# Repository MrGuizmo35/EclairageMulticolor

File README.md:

# EclairageMulticolor
Eclairage led RGB pour la petite maison de ma fille

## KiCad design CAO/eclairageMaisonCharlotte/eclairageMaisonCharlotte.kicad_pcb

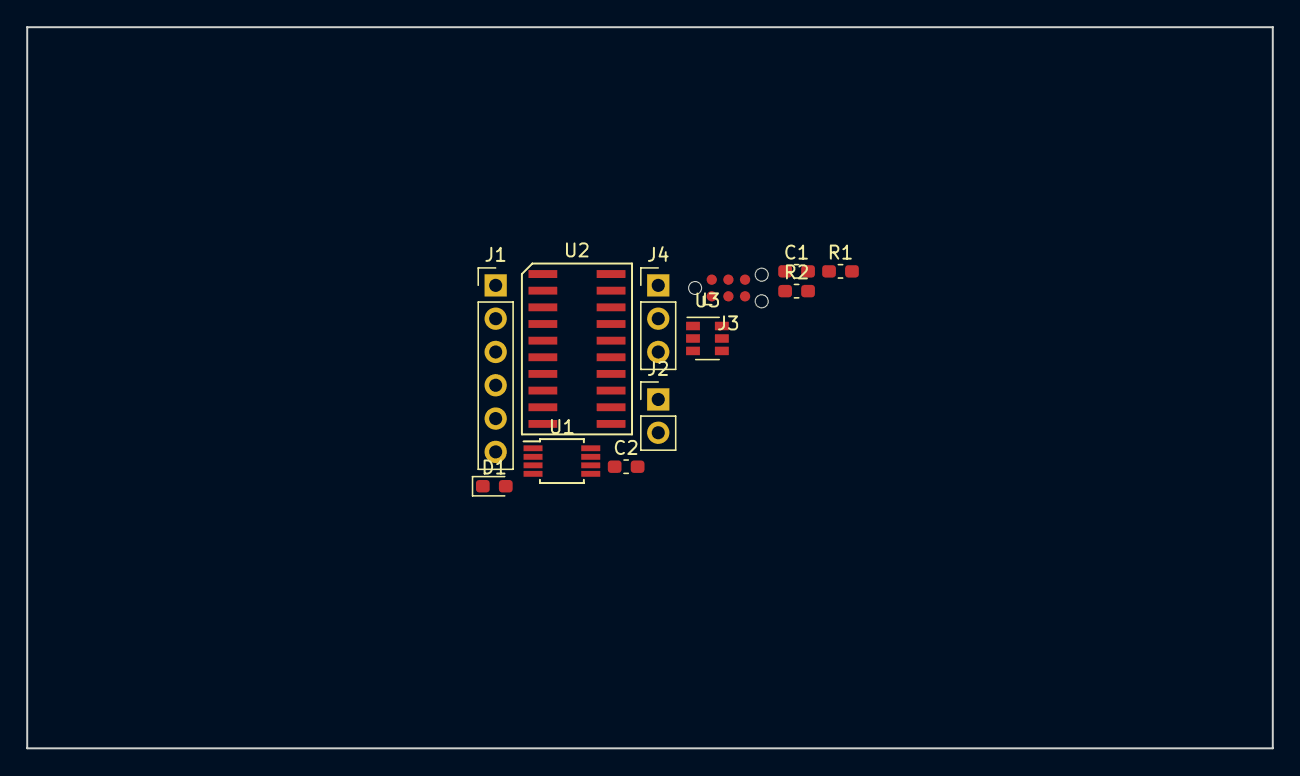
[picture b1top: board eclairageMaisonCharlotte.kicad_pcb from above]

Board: 2 copper layers, 95.0 x 55.0 mm, 12 parts (0 on the bottom side), 15 nets, no tracks yet.

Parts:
C1, C2: 1u; C_0603_1608Metric_Pad1.05x0.95mm_HandSolder
D1: LED; LED_0603_1608Metric_Pad1.05x0.95mm_HandSolder
J1: Conn_01x06; PinHeader_1x06_P2.54mm_Vertical
J2: Conn_01x02; PinHeader_1x02_P2.54mm_Vertical
J3: MCP_NL; Tag-Connect_TC2030-IDC-NL_2x03_P1.27mm_Vertical
J4: Conn_01x03; PinHeader_1x03_P2.54mm_Vertical
R1: 4k7; R_0603_1608Metric_Pad1.05x0.95mm_HandSolder
R2: 470; R_0603_1608Metric_Pad1.05x0.95mm_HandSolder
U1: DS18B20U; MSOP-8_3x3mm_P0.65mm
U2: PIC16F1618-19; SOIC-20
U3: SN74LVC1T45DBV; SOT-23-6

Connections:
+3V3: C2.1, J1.1, J3.2, R1.1, U1.8, U2.1, U3.1
+5V: C1.2, J1.2, J2.1, J4.1, U3.6
/ISPCLK: J3.5, U2.18
/ISPDAT: J3.4, U2.19
/~MCLR: J3.1, U2.4
GND: C1.1, C2.2, D1.1, J1.3, J2.2, J3.3, J4.3, U1.4, U2.20, U3.2
unnamed: D1.2, R2.2
unnamed: J1.4, U2.10
unnamed: J1.5, U2.11
unnamed: J1.6, U2.12
unnamed: J4.2, U3.4
unnamed: R1.2, U1.1, U2.2
unnamed: R2.1, U2.16
unnamed: U2.15, U3.5
unnamed: U2.17, U3.3

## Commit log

2018-11-12 Premier commit! Début de rédaction de firmware
2018-11-13 la communication serie doit etre operationnelle. A tester
2018-11-25 Firmware good enough. Serveur python good enough. Application labview good enough....
2018-11-25 Correction d'une faute de frappe dans automode. Limitation de la luminance à 0.2
